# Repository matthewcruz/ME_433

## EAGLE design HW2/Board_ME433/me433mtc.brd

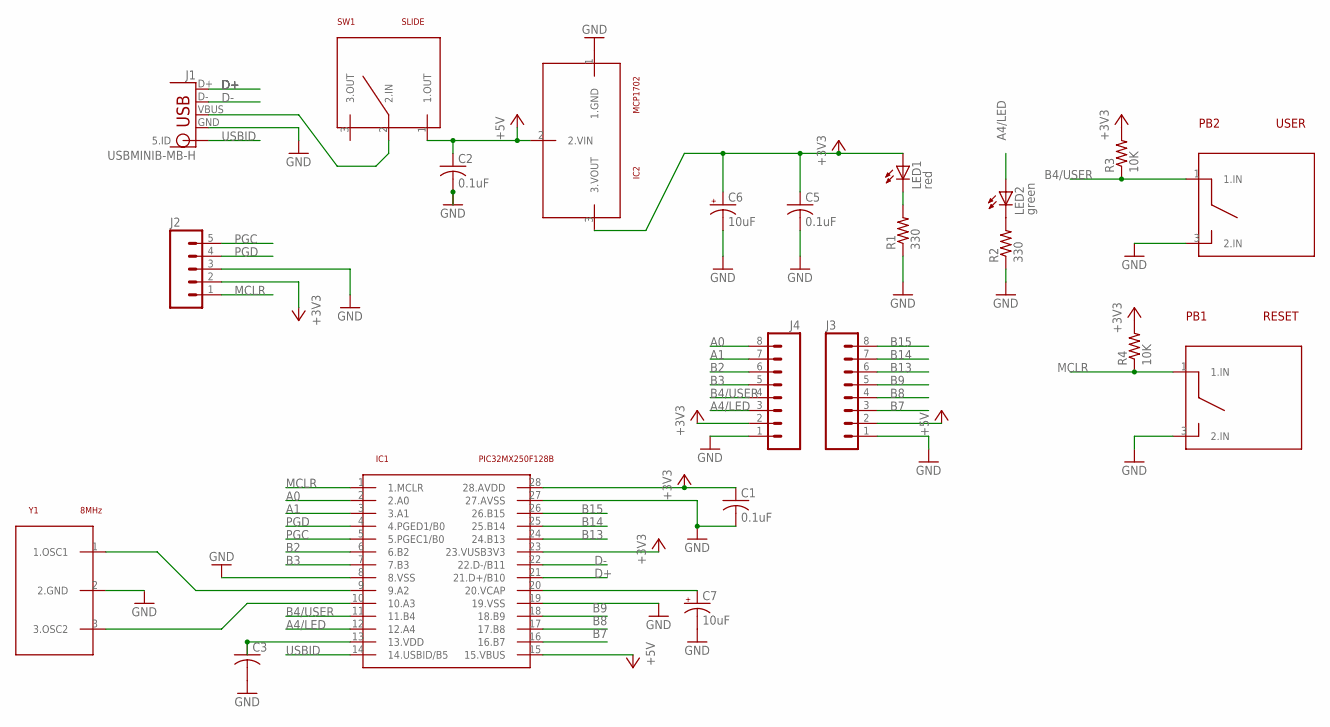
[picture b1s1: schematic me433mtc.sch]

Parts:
C1, C2, C5: 0.1uF; C025-025X050
C3: C-US025-025X050; C025-025X050
C6, C7: 10uF; B45181B
IC1: PIC32MX250F128B; DIL28-3
IC2: MCP1702; TO92
J1: USBMINIB-MB-H; USB-MB-H
J2: M05PTH; 1X05
J3, J4: M08; 1X08_ROUND
LED1: red; LED3MM
LED2: green; LED3MM
PB1: RESET; 1X03
PB2: USER; 1X03
R1, R2: 330; 0204/7
R3, R4: 10K; 0204/7
SW1: SLIDE; 1X03
Y1: 8MHz; 1X03

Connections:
+3V3: C1.1, C3.1, C5.1, C6.+, IC1.13 (13.VDD), IC1.23 (23.VUSB3V3), IC1.28 (28.AVDD), IC2.3 (3.VOUT), J2.2, J4.2, LED1.A, R3.2, R4.2
+5V: C2.1, IC1.15 (15.VBUS), IC2.2 (2.VIN), J3.2, SW1.1 (1.OUT)
A0: IC1.2 (2.A0), J4.8 (A0)
A1: IC1.3 (3.A1), J4.7
A4/LED: IC1.12 (12.A4), J4.3, LED2.A
B2: IC1.6 (6.B2), J4.6
B3: IC1.7 (7.B3), J4.5
B4/USER: IC1.11 (11.B4), J4.4, PB2.1 (1.IN), R3.1
B7: IC1.16 (16.B7), J3.3
B8: IC1.17 (17.B8), J3.4
B9: IC1.18 (18.B9), J3.5
B13: IC1.24 (24.B13), J3.6
B14: IC1.25 (25.B14), J3.7
B15: IC1.26 (26.B15), J3.8 (A0)
D+: IC1.21 (21.D+/B10), J1.D+ (1.GND)
D-: IC1.22 (22.D-/B11), J1.D- (2.ID)
GND: C1.2, C2.2, C3.2, C5.2, C6.-, C7.-, IC1.8 (8.VSS), IC1.19 (19.VSS), IC1.27 (27.AVSS), IC2.1 (1.GND), J1.GND (4.D-), J2.3, J3.1, J4.1, PB1.3 (2.IN), PB2.3 (2.IN), R1.1, R2.1, Y1.2 (2.GND)
MCLR: IC1.1 (1.MCLR), J2.1, PB1.1 (1.IN), R4.1
unnamed: IC1.9 (9.A2), Y1.1 (1.OSC1)
unnamed: J1.VBUS (3.D+), SW1.2 (2.IN)
unnamed: LED1.K (C), R1.2
unnamed: LED2.K (C), R2.2
unnamed: C7.+, IC1.20 (20.VCAP)
unnamed: IC1.10 (10.A3), Y1.3 (3.OSC2)
PGC: IC1.5 (5.PGEC1/B0), J2.5
PGD: IC1.4 (4.PGED1/B0), J2.4
USBID: IC1.14 (14.USBID/B5), J1.ID (5.ID)

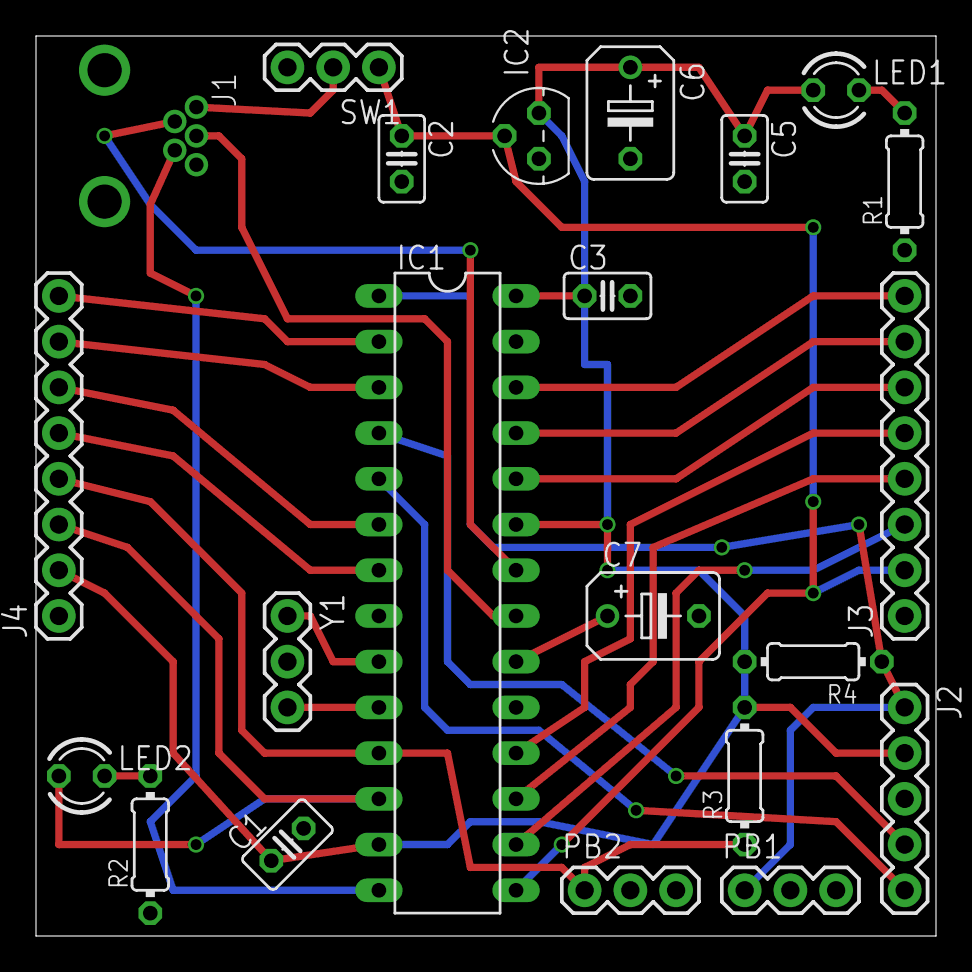
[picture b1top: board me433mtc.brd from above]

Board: 2 copper layers, 50.0 x 50.0 mm, 22 parts (0 on the bottom side), 27 nets.

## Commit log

2016-04-05 added empty project for MPLAB
2016-04-05 added empty project for MPLAB -2
2016-04-05 added empty project for MPLAB -3
2016-04-05 working Hello World
2016-04-05 add picture of circuit on breadboard
2016-04-14 library more complete schematic almost done
2016-04-14 finished schematic
2016-04-14 board is placed
2016-04-14 finished board
2016-04-14 Ready to be checked before order
2016-04-23 add hw3 and hw4 folder as well as picture of hw 1 schematic
2016-04-26 added HW4 with SPI working- need to test I2C
2016-04-28 added working i2C tested for output GPIO0
2016-04-28 got i2c working
2016-04-28 wiring picture and input and output on expander working
2016-04-29 added new project for IMU and wrote initGyro()
2016-05-01 updated main to try and get who_am_i working, wrote multiread function, added ISR
2016-05-02 who am i working - imu burned out
2016-05-11 have PWM and gyro multiread working
2016-05-13 added working LCD with IMU hw5
2016-05-13 fixed statement for Y
2016-05-17 updated HW5 and 6 with pictures of progress
2016-05-20 finished Android Hello World and Camera
2016-06-05 added nearly working code for android cam and serial working
2016-06-05 slider controlling PWM -- all done
2016-06-05 everything should be finished with COM affecting PWM
2016-06-09 all done
2016-06-09 finally all done
